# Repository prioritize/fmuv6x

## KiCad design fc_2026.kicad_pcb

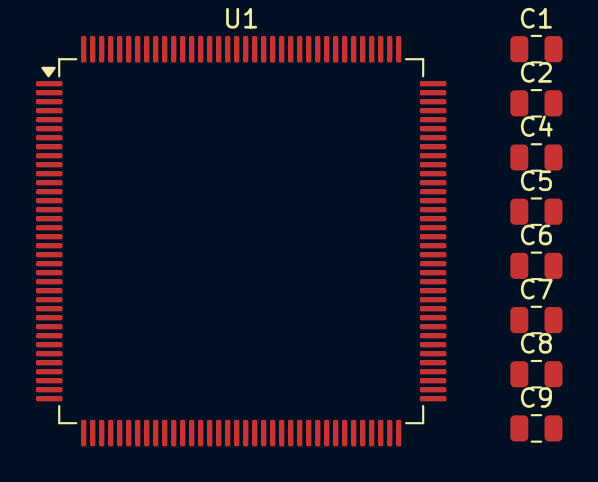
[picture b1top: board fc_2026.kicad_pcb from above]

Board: 2 copper layers, 9 parts (0 on the bottom side), 3 nets, no tracks yet.

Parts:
C1, C4, C6, C7: 2.2uF; C_0805_2012Metric
C2, C5, C8, C9: .1uF; C_0805_2012Metric
U1: STM32H753ZITx; LQFP-144_20x20mm_P0.5mm

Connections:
BATT_IN: C1.2, C2.2, C4.2, C5.2, C6.2, C7.2, C8.2, C9.2
GND: C1.1, C2.1, C4.1, C5.1, C6.1, C7.1, C8.1, C9.1
unnamed: U1.16 (VSS), U1.38 (VSS), U1.51 (VSS), U1.61 (VSS), U1.83 (VSS), U1.94 (VSS), U1.107 (VSS), U1.120 (VSS), U1.130 (VSS)

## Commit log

2026-01-09 Adding base schematics
2026-01-10 progress
2026-01-11 power zone 1 updates
